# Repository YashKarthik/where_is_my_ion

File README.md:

# Where is my ION???

## LED <-> Driver assignment

1. Driver 1 - 16
    + [x] 1: Conestoga Mall
    + [x] 2: conn to northfield
    + [x] 1: Northfield
    + [x] 3: northfield to r&t
    + [x] 1: R & T
    + [x] 2: r&t to uw
    + [x] 1: UW
    + [x] 1: uw to laurier-waterloo park
    + [x] 1: Laurier-Waterloo Park Stn.
    + [x] 1: laurier-waterloo park to willis way
    + [x] 1: Willis Way Stn.
    + [x] 1: Allen Stn.

2. Driver 2 - 16
    + [x] 1: allen to grh
    + [x] 1: GRH Stn.
    + [x] 2: grh to central
    + [x] 1: Central Stn.
    + [x] 1: Victoria Stn.
    + [x] 1: Queen Stn.
    + [x] 1: Kitchener-Market Stn.
    + [x] 2: kitchener-market to borden
    + [x] 1: Borden Stn.
    + [x] 2: borden to mill
    + [x] 1: Mill Stn.
    + 
    +

3. Driver 3 - 16
    + [x] 3: mill to block line
    + [x] 1: Block Line Stn.
    + [x] 3: block line to fairway
    + [x] 1: Fairway Stn.
-----------reverse
    + [x] 1: Fairway Stn.
    + [x] 3: fairway to block line
    + [x] 1: Block Line Stn.
    + [x] 3: block line to mill

4. Driver 4 - 16
    + [x] 1: Mill Stn.
    + [x] 1: mill to borden
    + [x] 1: Borden Stn.
    + [x] 2: borden to kitchener-market
    + [x] 1: Kitchener-Market Stn.
    + [x] 0: kitchener-market to frederick
    + [x] 1: Frederick Stn.
    + [x] 0: frederick to kitchener city hall
    + [x] 1: Kitchener City Hall Stn.
    + [x] 0: kitchener city hall to central station
    + [x] 1: Central Stn.
    + [x] 2: central to grand river hospital
    + [x] 1: Grand River Hospital Stn.
    + [x] 1: grand river hospital to allen
    + [x] 1: Allen Stn.
    + [x] 0: allen to waterloo public square
    + [x] 1: Waterloo Public Square Stn.
    + [x] 1: waterloo public square to laurier-waterloo park

5. Driver 5 - 14
    + [x] 1: Laurier-Waterloo Park Stn.
    + [x] 1: laurier-waterloo park to university of waterloo
    + [x] 1: University of Waterloo Stn.
    + [x] 2: university of waterloo to research & tech
    + [x] 1: Research & Tech Stn.
    + [x] 3: research & tech to northfield
    + [x] 1: Northfield Stn.
    + [x] 2: northfield to conestoga
    + [x] 1: Conestoga Stn.
    + [x] 1: WIFI (on/off green)

## Num. LED Calculations

- [x] 16 station leds (c -> f) (blue)
- [x] 16 station leds (f -> c) (blue)
- [x] 21 inter-station leds (c -> f) (white)
- [x] 21 inter-station leds (f -> c) (white)
- [x] 1 red/green => 2 leds (power (ON/OFF))
- [x] 1 green wifi (ON/OFF)

= 78/80 used

### Inter-station LEDs

Conestoga to Fairway
- Conestoga to Northfield: 2 leds
- Northfield to Research & Tech: 3 leds
- Research & Tech to University of Waterloo: 2 leds
- University of Waterloo to Laurier-Waterloo Park: 1 led
- Laurier-Waterloo Park to Willis Way: 1 led
- Willis Way to Allen: 0 led
- Allen to Grand River Hospital: 1 led
- Grand River Hospital to Central Station: 2 leds
- Central Station to Victoria Park (0 led)
- Victoria Park to Queen (0 led)
- Queen to Kitchener-Market (0 led)
- Kitchener Market to Borden (2 led)
- Borden to Mill (1 led)
- Mill to Block Line (3 leds)
- Block Line to Fairway (3 ledss)

Fairway to Conestoga
- Fairway to block line (3 leds)
- Block Line to Mill (3 leds)
- Mill to Borden (1 led)
- Borden to Kitchener-Market (2 led)
- Kitchener-Market to Frederick (0 led)
- Frederick to Kitchener City Hall (0 led)
- Kitchener City Hall to Central Station (0 led)
- Central Station to Grand River Hospital:  2 leds
- Grand River Hospital to Allen: 1 led
- Allen to Waterloo Public Sq: 0 led
- Waterloo Public Sq to Laurier-Waterloo Park: 1 led
- Laurier-Waterloo Park to University of Waterloo to : 1 led
- University of Waterloo to Research & Tech:  2 leds
- Research & Tech to Northfield: 3 leds
- Northfield to Conestoga:  2 leds

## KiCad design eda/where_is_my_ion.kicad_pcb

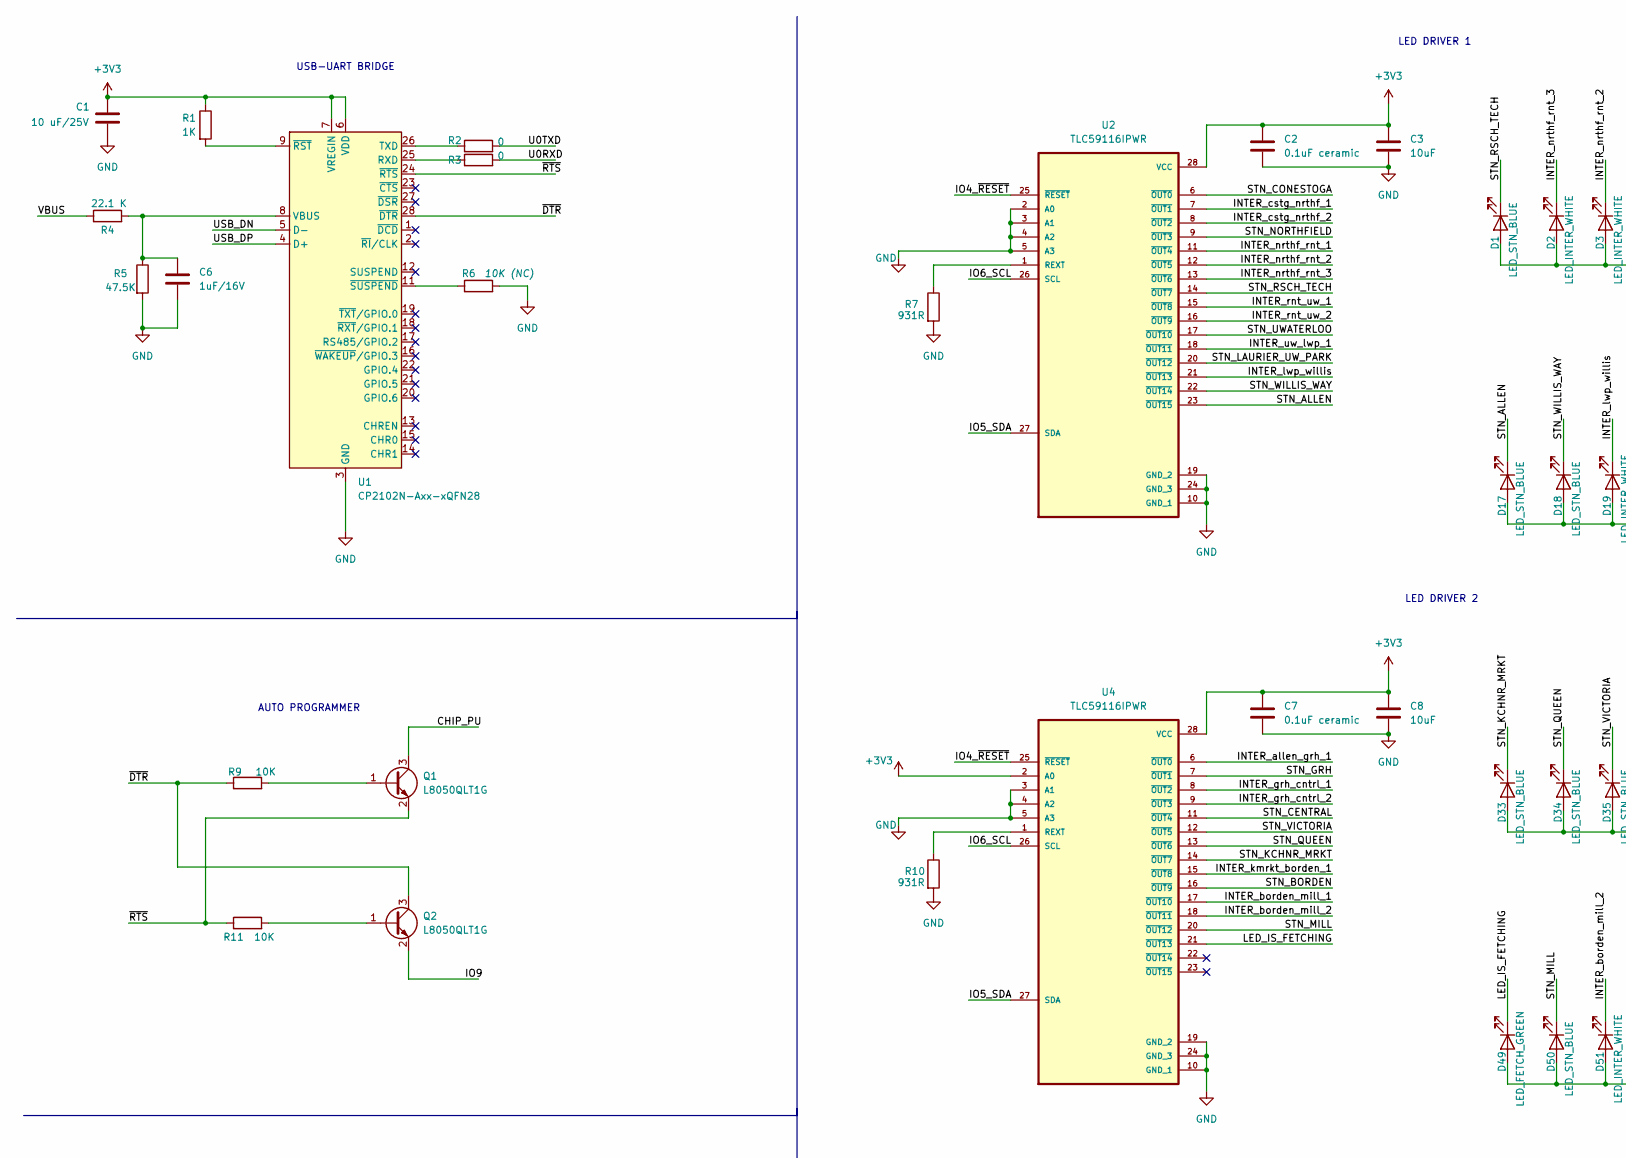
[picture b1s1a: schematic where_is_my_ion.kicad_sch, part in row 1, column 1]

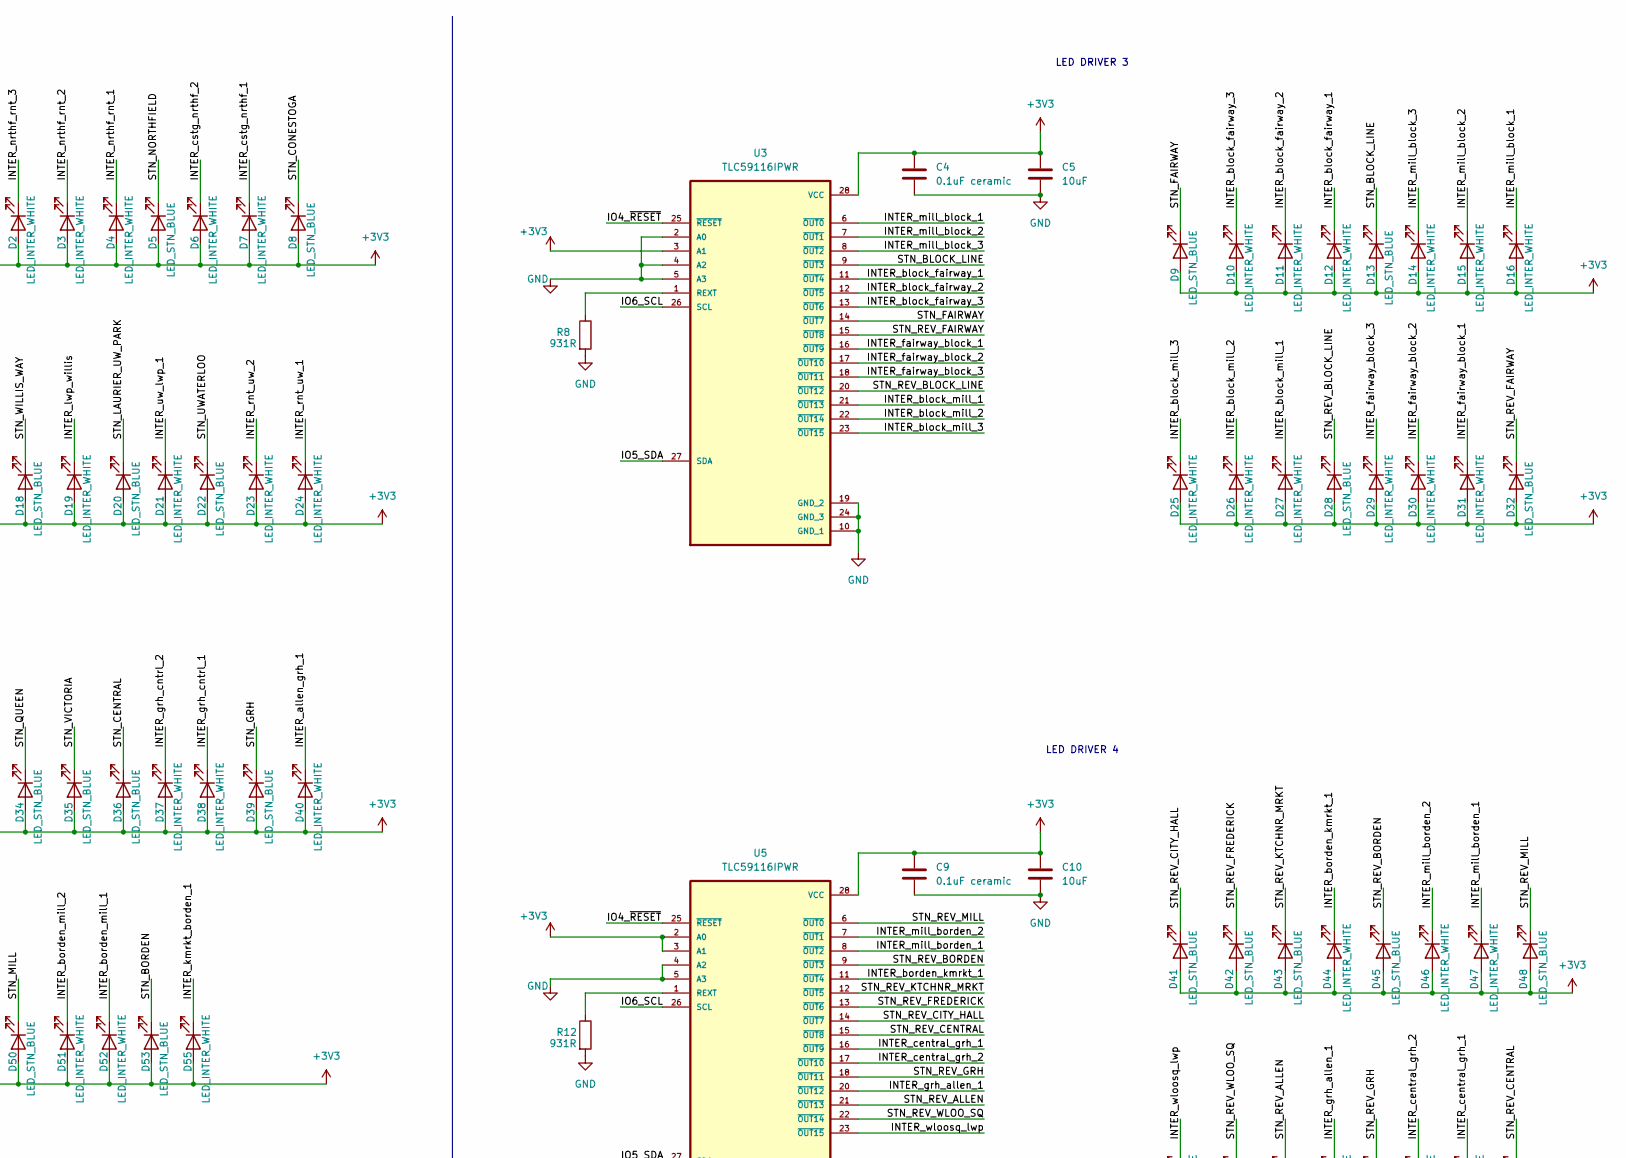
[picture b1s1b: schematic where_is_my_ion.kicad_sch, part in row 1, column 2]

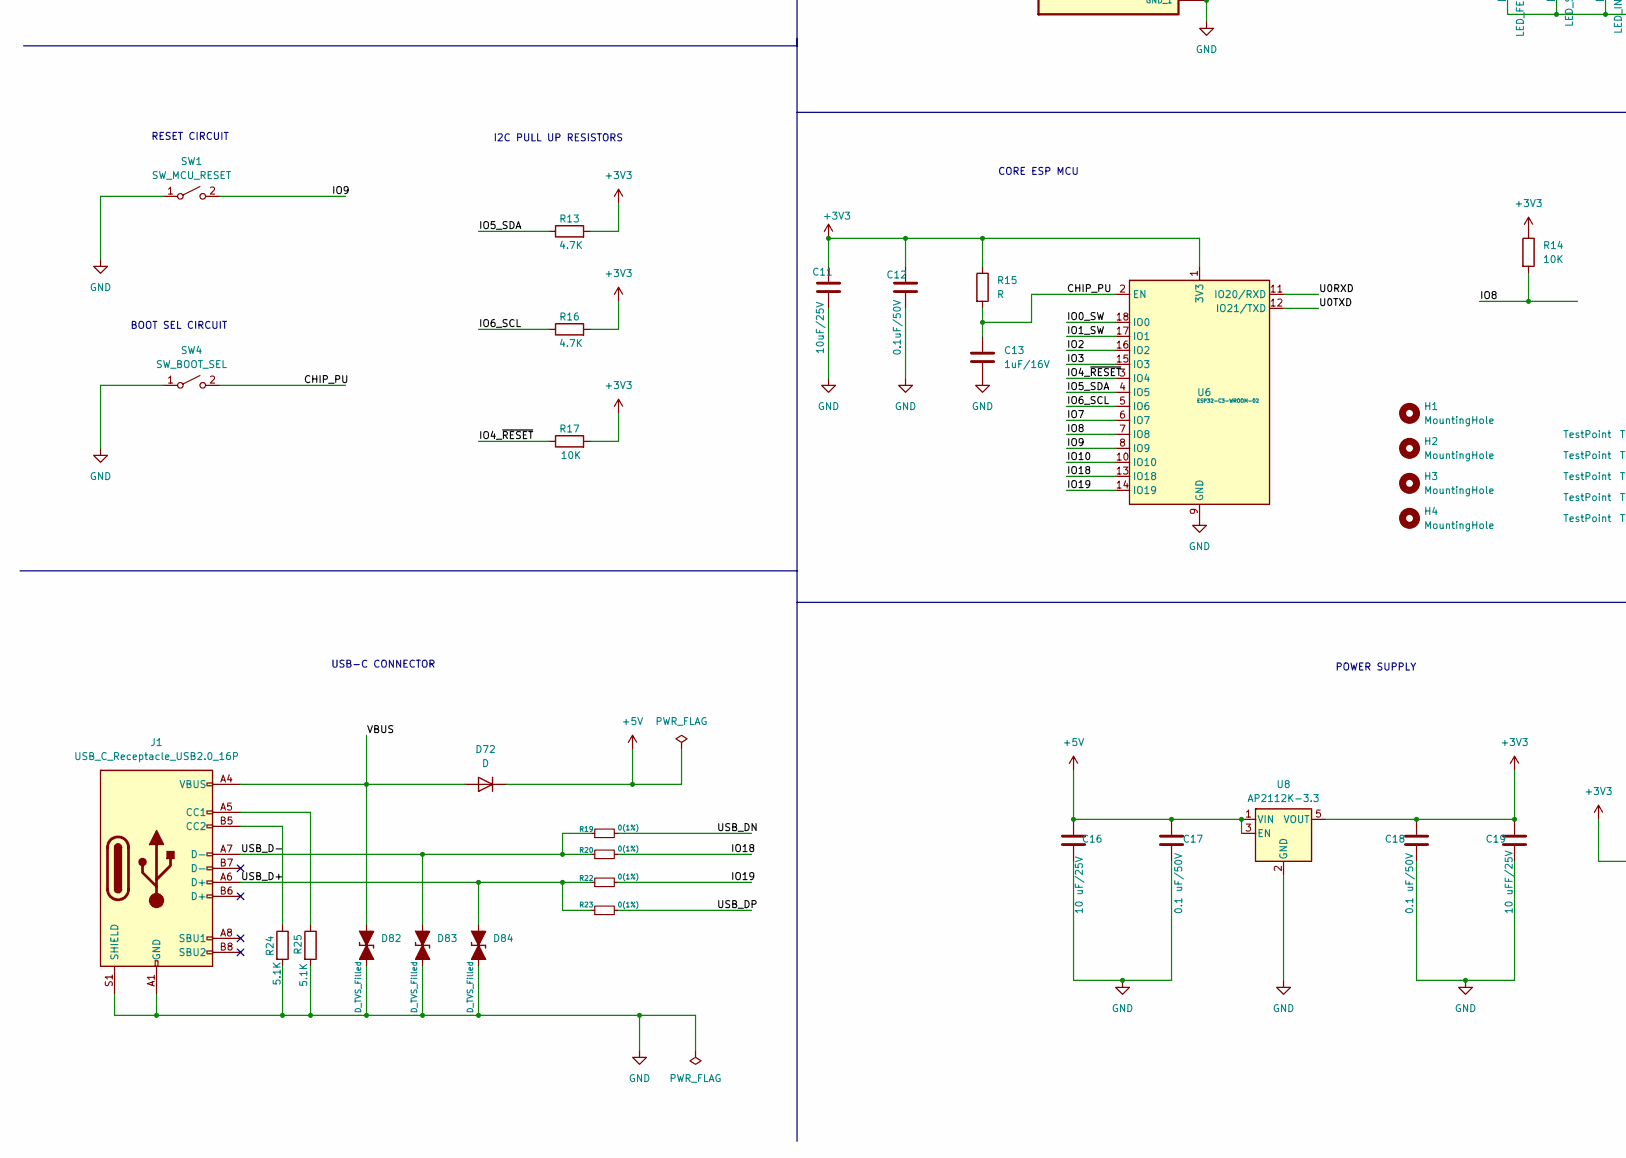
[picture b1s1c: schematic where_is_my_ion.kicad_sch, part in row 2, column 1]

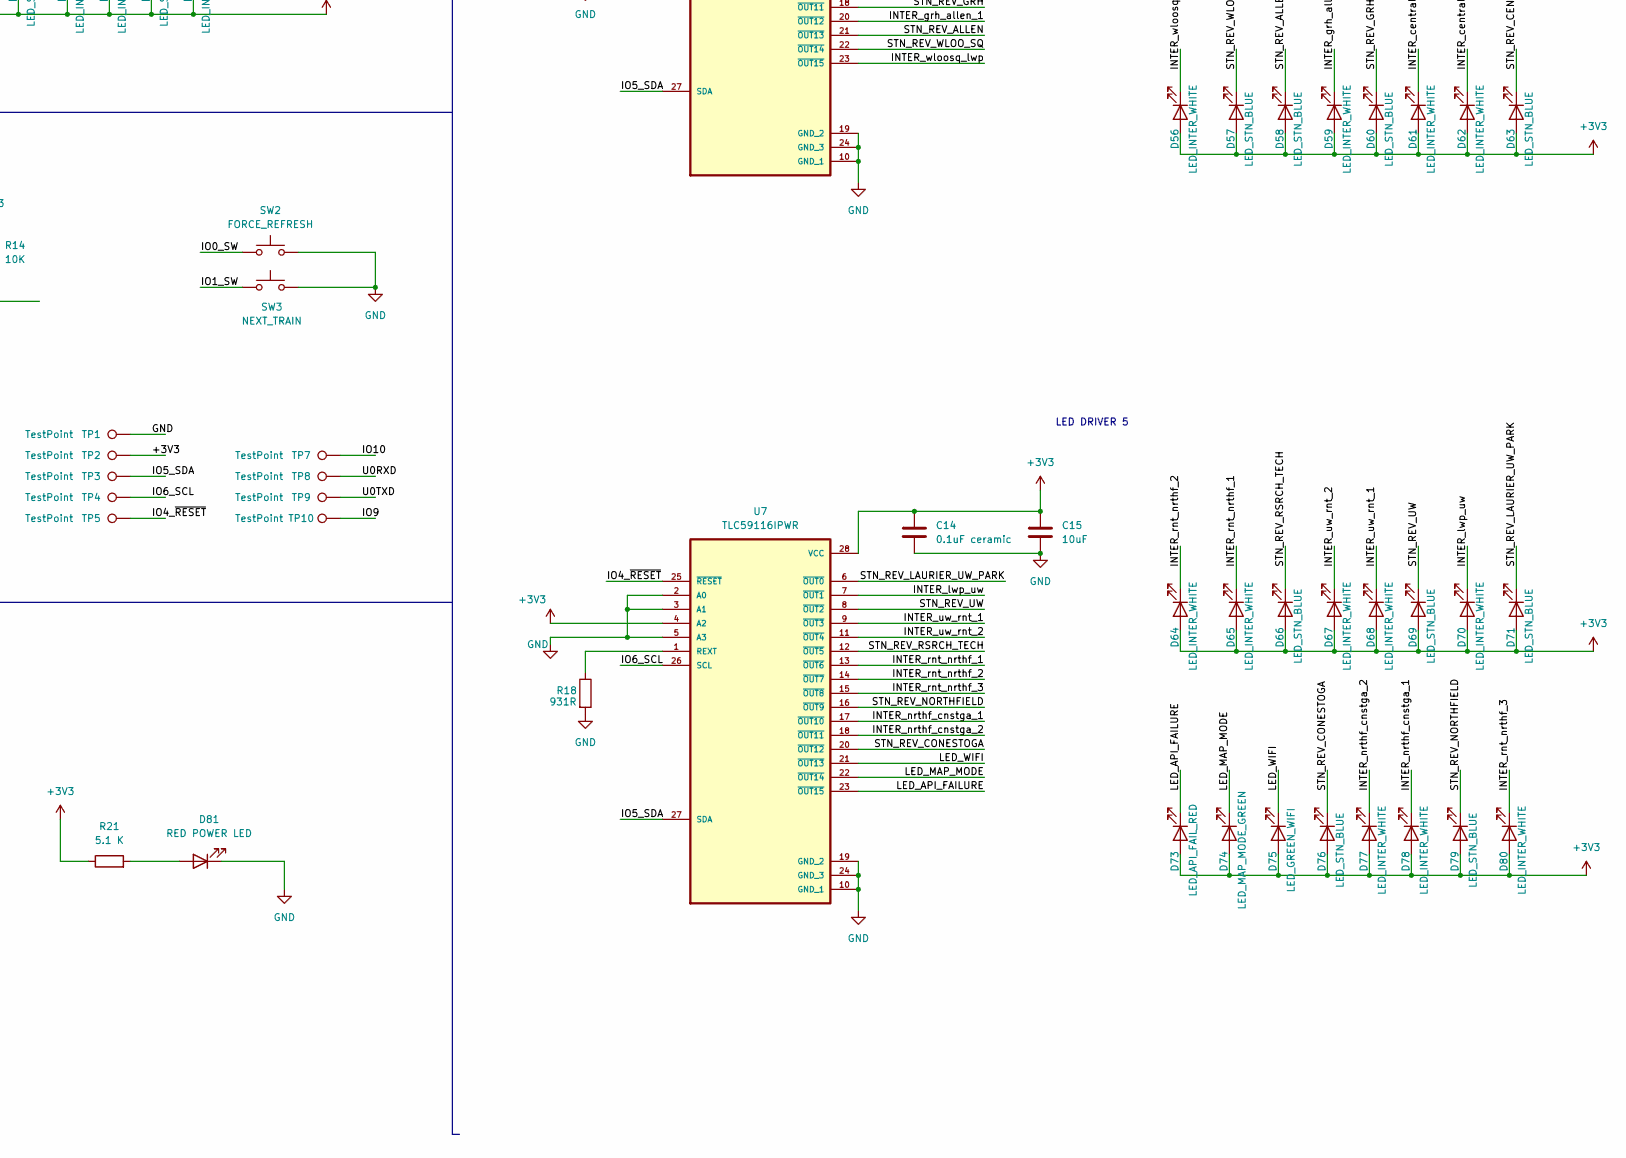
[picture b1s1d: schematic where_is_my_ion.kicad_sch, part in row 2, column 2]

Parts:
C1: 10 uF/25V; CP_EIA-3528-15_AVX-H; LCSC Part Num. C22387953
C2, C4, C7, C9, C14: 0.1uF ceramic; C_0603_1608Metric
C3, C5, C8, C10, C15: 10uF; CP_EIA-3528-15_AVX-H
C6, C13: 1uF/16V; C_0805_2012Metric; LCSC Part Num. C24123
C11: 10uF/25V; CP_EIA-3528-15_AVX-H; LCSC Part Num. C22387953
C12: 0.1uF/50V; C_0603_1608Metric; LCSC Part Num. C3011652
C16: 10 uF/25V; CP_EIA-3528-15_AVX-H
C17, C18: 0.1 uF/50V; C_0603_1608Metric
C19: 10 uFF/25V; CP_EIA-3528-15_AVX-H
D1: LED_STN_BLUE; LED_0603_1608Metric; LCSC Part Num. C497940
D2: LED_INTER_WHITE; LED_0603_1608Metric; LCSC Part Num. C965808
D3, D4, D6, D7, D10, D11, D12, D14, D15, D16, D19, D21, D23, D24, D25, D26, D27, D29, D30, D31, D37, D38, D40, D44, D46, D47, D51, D52, D55, D56, D59, D61, D62, D64, D65, D67, D68, D70, D77, D78, D80: LED_INTER_WHITE; LED_0603_1608Metric
D5, D8, D9, D13, D17, D18, D20, D22, D28, D32, D33, D34, D35, D36, D39, D41, D42, D43, D45, D48, D50, D53, D57, D58, D60, D63, D66, D69, D71, D76, D79: LED_STN_BLUE; LED_0603_1608Metric
D49: LED_FETCH_GREEN; LED_0603_1608Metric; LCSC Part Num. C7429914
D72: D; D_SOD-123; LCSC Part Num. C82544
D73: LED_API_FAIL_RED; LED_0603_1608Metric
D74: LED_MAP_MODE_GREEN; LED_0603_1608Metric
D75: LED_GREEN_WIFI; LED_0603_1608Metric
D81: RED POWER LED; LED_0603_1608Metric; LCSC Part Num. C965799
D82: D_TVS_Filled; D_SOD-523; LCSC Part Num. C383211
D83, D84: D_TVS_Filled; D_SOD-523
H1, H2, H3, H4: MountingHole; MountingHole_2.2mm_M2
J1: USB_C_Receptacle_USB2.0_16P; USB_C_Receptacle_HRO_TYPE-C-31-M-12
Q1, Q2: L8050QLT1G; SOT-23
R1: 1K; R_0603_1608Metric; LCSC Part Num. C22548
R2, R3: 0; R_0603_1608Metric
R4: 22.1 K; R_0603_1608Metric; LCSC Part Num. C137768
R5: 47.5K; R_0603_1608Metric; LCSC Part Num. C2933225
R6: 10K (NC); R_0603_1608Metric
R7, R8, R10, R12, R18: 931R; R_0603_1608Metric
R9, R11, R14, R17: 10K; R_0603_1608Metric
R13, R16: 4.7K; R_0603_1608Metric
R15: R; R_0603_1608Metric
R19, R20, R22, R23: 0(1%); R_0603_1608Metric
R21: 5.1 K; R_0603_1608Metric
R24, R25: 5.1K; R_0603_1608Metric
SW1: SW_MCU_RESET; SW_TS-1088-AR02016_1
SW2: FORCE_REFRESH; SW_TS-1088-AR02016_1
SW3: NEXT_TRAIN; SW_TS-1088-AR02016_1
SW4: SW_BOOT_SEL; SW_TS-1088-AR02016_1
TP1, TP2, TP3, TP4, TP5, TP7, TP8, TP9, TP10: TestPoint; TestPoint_Pad_D2.0mm
U1: CP2102N-Axx-xQFN28; QFN-28-1EP_5x5mm_P0.5mm_EP3.35x3.35mm
U2, U3, U4, U5, U7: TLC59116IPWR; SOP65P640X120-28N
U6: ESP32-C3-WROOM-02
U8: AP2112K-3.3; SOT-23-5

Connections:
+3V3: C1.1, C2.1, C3.1, C4.1, C5.1, C7.1, C8.1, C9.1, C10.1, C11.1, C12.1, C14.1, C15.1, C18.2, C19.1, D1.2 (A), D2.2 (A), D3.2 (A), D4.2 (A), D5.2 (A), D6.2 (A), D7.2 (A), D8.2 (A), D9.2 (A), D10.2 (A), D11.2 (A), D12.2 (A), D13.2 (A), D14.2 (A), D15.2 (A), D16.2 (A), D17.2 (A), D18.2 (A), D19.2 (A), D20.2 (A), D21.2 (A), D22.2 (A), D23.2 (A), D24.2 (A), D25.2 (A), D26.2 (A), D27.2 (A), D28.2 (A), D29.2 (A), D30.2 (A), D31.2 (A), D32.2 (A), D33.2 (A), D34.2 (A), D35.2 (A), D36.2 (A), D37.2 (A), D38.2 (A), D39.2 (A), D40.2 (A), D41.2 (A), D42.2 (A), D43.2 (A), D44.2 (A), D45.2 (A), D46.2 (A), D47.2 (A), D48.2 (A), D49.2 (A), D50.2 (A), D51.2 (A), D52.2 (A), D53.2 (A), D55.2 (A), D56.2 (A), D57.2 (A), D58.2 (A), D59.2 (A), D60.2 (A), D61.2 (A), D62.2 (A), D63.2 (A), D64.2 (A), D65.2 (A), D66.2 (A), D67.2 (A), D68.2 (A), D69.2 (A), D70.2 (A), D71.2 (A), D73.2 (A), D74.2 (A), D75.2 (A), D76.2 (A), D77.2 (A), D78.2 (A), D79.2 (A), D80.2 (A), R1.1, R13.2, R14.1, R15.1, R16.2, R17.2, R21.1, TP2.1, U1.6 (VDD), U1.7 (VREGIN), U2.28 (VCC), U3.3 (A1), U3.28 (VCC), U4.2 (A0), U4.28 (VCC), U5.2 (A0), U5.3 (A1), U5.28 (VCC), U6.1 (3V3), U7.4 (A2), U7.28 (VCC), U8.5 (VOUT)
+5V: C16.1, C17.2, D72.1 (K), U8.1 (VIN), U8.3 (EN)
/CHIP_PU: C13.1, Q1.3 (C), R15.2, SW4.2 (B), U6.2 (EN)
/INTER_allen_grh_1: D40.1 (K), U4.6 (~OUT0)
/INTER_block_fairway_1: D12.1 (K), U3.11 (~OUT4)
/INTER_block_fairway_2: D11.1 (K), U3.12 (~OUT5)
/INTER_block_fairway_3: D10.1 (K), U3.13 (~OUT6)
/INTER_block_mill_1: D27.1 (K), U3.21 (~OUT13)
/INTER_block_mill_2: D26.1 (K), U3.22 (~OUT14)
/INTER_block_mill_3: D25.1 (K), U3.23 (~OUT15)
/INTER_borden_kmrkt_1: D44.1 (K), U5.11 (~OUT4)
/INTER_borden_mill_1: D52.1 (K), U4.17 (~OUT10)
/INTER_borden_mill_2: D51.1 (K), U4.18 (~OUT11)
/INTER_central_grh_1: D62.1 (K), U5.16 (~OUT9)
/INTER_central_grh_2: D61.1 (K), U5.17 (~OUT10)
/INTER_cstg_nrthf_1: D7.1 (K), U2.7 (~OUT1)
/INTER_cstg_nrthf_2: D6.1 (K), U2.8 (~OUT2)
/INTER_fairway_block_1: D31.1 (K), U3.16 (~OUT9)
/INTER_fairway_block_2: D30.1 (K), U3.17 (~OUT10)
/INTER_fairway_block_3: D29.1 (K), U3.18 (~OUT11)
/INTER_grh_allen_1: D59.1 (K), U5.20 (~OUT12)
/INTER_grh_cntrl_1: D38.1 (K), U4.8 (~OUT2)
/INTER_grh_cntrl_2: D37.1 (K), U4.9 (~OUT3)
/INTER_kmrkt_borden_1: D55.1 (K), U4.15 (~OUT8)
/INTER_lwp_uw: D70.1 (K), U7.7 (~OUT1)
/INTER_lwp_willis: D19.1 (K), U2.21 (~OUT13)
/INTER_mill_block_1: D16.1 (K), U3.6 (~OUT0)
/INTER_mill_block_2: D15.1 (K), U3.7 (~OUT1)
/INTER_mill_block_3: D14.1 (K), U3.8 (~OUT2)
/INTER_mill_borden_1: D47.1 (K), U5.8 (~OUT2)
/INTER_mill_borden_2: D46.1 (K), U5.7 (~OUT1)
/INTER_nrthf_cnstga_1: D78.1 (K), U7.17 (~OUT10)
/INTER_nrthf_cnstga_2: D77.1 (K), U7.18 (~OUT11)
/INTER_nrthf_rnt_1: D4.1 (K), U2.11 (~OUT4)
/INTER_nrthf_rnt_2: D3.1 (K), U2.12 (~OUT5)
/INTER_nrthf_rnt_3: D2.1 (K), U2.13 (~OUT6)
/INTER_rnt_nrthf_1: D65.1 (K), U7.13 (~OUT6)
/INTER_rnt_nrthf_2: D64.1 (K), U7.14 (~OUT7)
/INTER_rnt_nrthf_3: D80.1 (K), U7.15 (~OUT8)
/INTER_rnt_uw_1: D24.1 (K), U2.15 (~OUT8)
/INTER_rnt_uw_2: D23.1 (K), U2.16 (~OUT9)
/INTER_uw_lwp_1: D21.1 (K), U2.18 (~OUT11)
/INTER_uw_rnt_1: D68.1 (K), U7.9 (~OUT3)
/INTER_uw_rnt_2: D67.1 (K), U7.11 (~OUT4)
/INTER_wloosq_lwp: D56.1 (K), U5.23 (~OUT15)
/IO0_SW: SW2.1, U6.18 (IO0)
/IO1_SW: SW3.1, U6.17 (IO1)
/IO2: U6.16 (IO2)
/IO3: U6.15 (IO3)
/IO4_~RESET: R17.1, TP5.1, U2.25 (~RESET), U3.25 (~RESET), U4.25 (~RESET), U5.25 (~RESET), U6.3 (IO4), U7.25 (~RESET)
/IO5_SDA: R13.1, TP3.1, U2.27 (SDA), U3.27 (SDA), U4.27 (SDA), U5.27 (SDA), U6.4 (IO5), U7.27 (SDA)
/IO6_SCL: R16.1, TP4.1, U2.26 (SCL), U3.26 (SCL), U4.26 (SCL), U5.26 (SCL), U6.5 (IO6), U7.26 (SCL)
/IO7: U6.6 (IO7)
/IO8: R14.2, U6.7 (IO8)
/IO9: Q2.2 (E), SW1.2 (B), TP10.1, U6.8 (IO9)
/IO10: TP7.1, U6.10 (IO10)
/IO18: R20.2, U6.13 (IO18)
/IO19: R22.2, U6.14 (IO19)
/LED_API_FAILURE: D73.1 (K), U7.23 (~OUT15)
/LED_IS_FETCHING: D49.1 (K), U4.21 (~OUT13)
/LED_MAP_MODE: D74.1 (K), U7.22 (~OUT14)
/LED_WIFI: D75.1 (K), U7.21 (~OUT13)
/STN_ALLEN: D17.1 (K), U2.23 (~OUT15)
/STN_BLOCK_LINE: D13.1 (K), U3.9 (~OUT3)
/STN_BORDEN: D53.1 (K), U4.16 (~OUT9)
/STN_CENTRAL: D36.1 (K), U4.11 (~OUT4)
/STN_CONESTOGA: D8.1 (K), U2.6 (~OUT0)
/STN_FAIRWAY: D9.1 (K), U3.14 (~OUT7)
/STN_GRH: D39.1 (K), U4.7 (~OUT1)
/STN_KCHNR_MRKT: D33.1 (K), U4.14 (~OUT7)
/STN_LAURIER_UW_PARK: D20.1 (K), U2.20 (~OUT12)
/STN_MILL: D50.1 (K), U4.20 (~OUT12)
/STN_NORTHFIELD: D5.1 (K), U2.9 (~OUT3)
/STN_QUEEN: D34.1 (K), U4.13 (~OUT6)
/STN_REV_ALLEN: D58.1 (K), U5.21 (~OUT13)
/STN_REV_BLOCK_LINE: D28.1 (K), U3.20 (~OUT12)
/STN_REV_BORDEN: D45.1 (K), U5.9 (~OUT3)
/STN_REV_CENTRAL: D63.1 (K), U5.15 (~OUT8)
/STN_REV_CITY_HALL: D41.1 (K), U5.14 (~OUT7)
/STN_REV_CONESTOGA: D76.1 (K), U7.20 (~OUT12)
/STN_REV_FAIRWAY: D32.1 (K), U3.15 (~OUT8)
/STN_REV_FREDERICK: D42.1 (K), U5.13 (~OUT6)
/STN_REV_GRH: D60.1 (K), U5.18 (~OUT11)
/STN_REV_KTCHNR_MRKT: D43.1 (K), U5.12 (~OUT5)
/STN_REV_LAURIER_UW_PARK: D71.1 (K), U7.6 (~OUT0)
/STN_REV_MILL: D48.1 (K), U5.6 (~OUT0)
/STN_REV_NORTHFIELD: D79.1 (K), U7.16 (~OUT9)
/STN_REV_RSRCH_TECH: D66.1 (K), U7.12 (~OUT5)
/STN_REV_UW: D69.1 (K), U7.8 (~OUT2)
/STN_REV_WLOO_SQ: D57.1 (K), U5.22 (~OUT14)
/STN_RSCH_TECH: D1.1 (K), U2.14 (~OUT7)
/STN_UWATERLOO: D22.1 (K), U2.17 (~OUT10)
/STN_VICTORIA: D35.1 (K), U4.12 (~OUT5)
/STN_WILLIS_WAY: D18.1 (K), U2.22 (~OUT14)
/U0RXD: R3.2, TP8.1, U6.11 (IO20/RXD)
/U0TXD: R2.2, TP9.1, U6.12 (IO21/TXD)
/USB_D+: D84.2 (A2), J1.A6 (D+), R22.1, R23.1
/USB_D-: D83.2 (A2), J1.A7 (D-), R19.1, R20.1
/USB_DN: R19.2, U1.5 (D-)
/USB_DP: R23.2, U1.4 (D+)
/VBUS: D72.2 (A), D82.2 (A2), J1.A4 (VBUS), J1.A9 (VBUS), J1.B4 (VBUS), J1.B9 (VBUS), R4.1
/~DTR: Q2.3 (C), R9.1, U1.28 (~DTR)
/~RTS: Q1.2 (E), R11.1, U1.24 (~RTS)
GND: C1.2, C2.2, C3.2, C4.2, C5.2, C6.2, C7.2, C8.2, C9.2, C10.2, C11.2, C12.2, C13.2, C14.2, C15.2, C16.2, C17.1, C18.1, C19.2, D81.1 (K), D82.1 (A1), D83.1 (A1), D84.1 (A1), J1.A1 (GND), J1.A12 (GND), J1.B1 (GND), J1.B12 (GND), J1.S1 (SHIELD), R5.2, R6.2, R7.2, R8.2, R10.2, R12.2, R18.2, R24.2, R25.2, SW1.1 (A), SW2.2, SW3.2, SW4.1 (A), TP1.1, U1.3 (GND), U1.29 (GND), U2.2 (A0), U2.3 (A1), U2.4 (A2), U2.5 (A3), U2.10 (GND_1), U2.19 (GND_2), U2.24 (GND_3), U3.2 (A0), U3.4 (A2), U3.5 (A3), U3.10 (GND_1), U3.19 (GND_2), U3.24 (GND_3), U4.3 (A1), U4.4 (A2), U4.5 (A3), U4.10 (GND_1), U4.19 (GND_2), U4.24 (GND_3), U5.4 (A2), U5.5 (A3), U5.10 (GND_1), U5.19 (GND_2), U5.24 (GND_3), U6.9 (GND), U6.19 (GND), U7.2 (A0), U7.3 (A1), U7.5 (A3), U7.10 (GND_1), U7.19 (GND_2), U7.24 (GND_3), U8.2 (GND)
unnamed: D81.2 (A), R21.2
unnamed: J1.A5 (CC1), R25.1
unnamed: J1.B5 (CC2), R24.1
unnamed: Q1.1 (B), R9.2
unnamed: Q2.1 (B), R11.2
unnamed: R3.1, U1.25 (RXD)
unnamed: R2.1, U1.26 (TXD)
unnamed: C6.1, R4.2, R5.1, U1.8 (VBUS)
unnamed: R1.2, U1.9 (~RST)
unnamed: R6.1, U1.11 (~SUSPEND)
unnamed: R7.1, U2.1 (REXT)
unnamed: R8.1, U3.1 (REXT)
unnamed: R10.1, U4.1 (REXT)
unnamed: R12.1, U5.1 (REXT)
unnamed: R18.1, U7.1 (REXT)

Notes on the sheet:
USB-C CONNECTOR
BOOT SEL CIRCUIT
AUTO PROGRAMMER
LED DRIVER 1
LED DRIVER 2
RESET CIRCUIT
POWER SUPPLY
LED DRIVER 5
USB-UART BRIDGE
LED DRIVER 4
LED DRIVER 3
I2C PULL UP RESISTORS
CORE ESP MCU

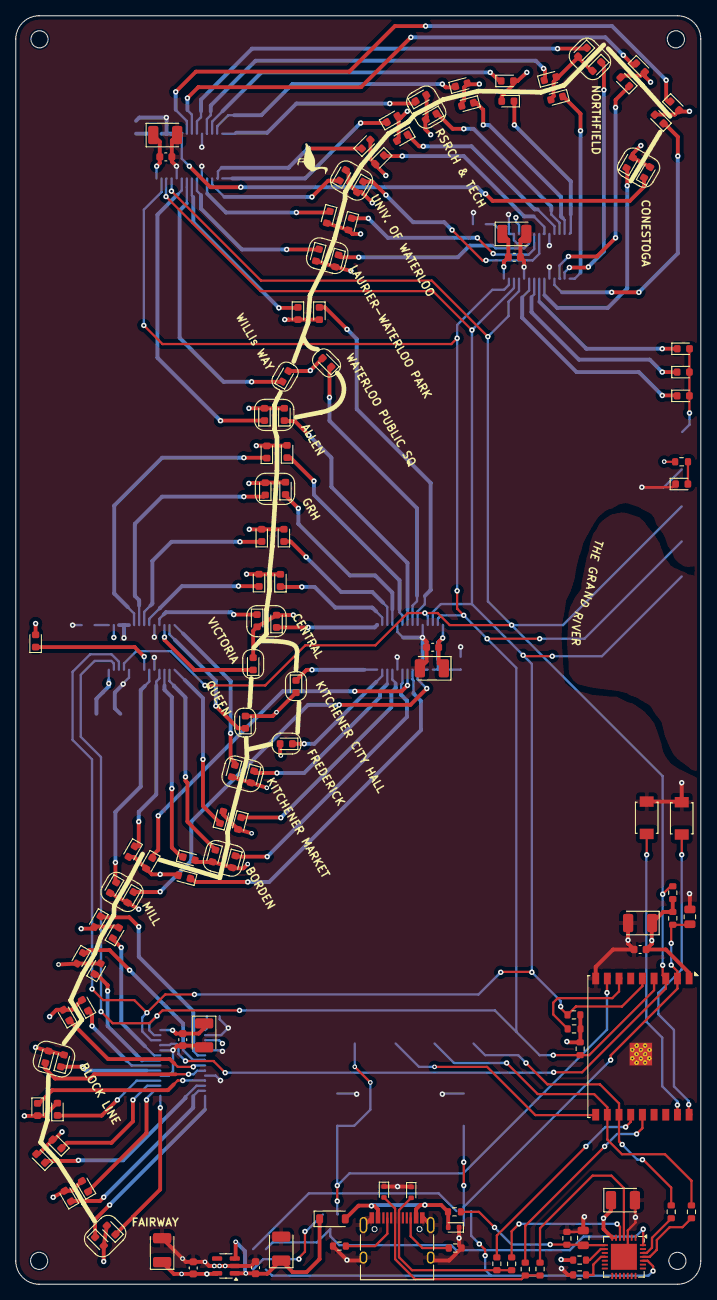
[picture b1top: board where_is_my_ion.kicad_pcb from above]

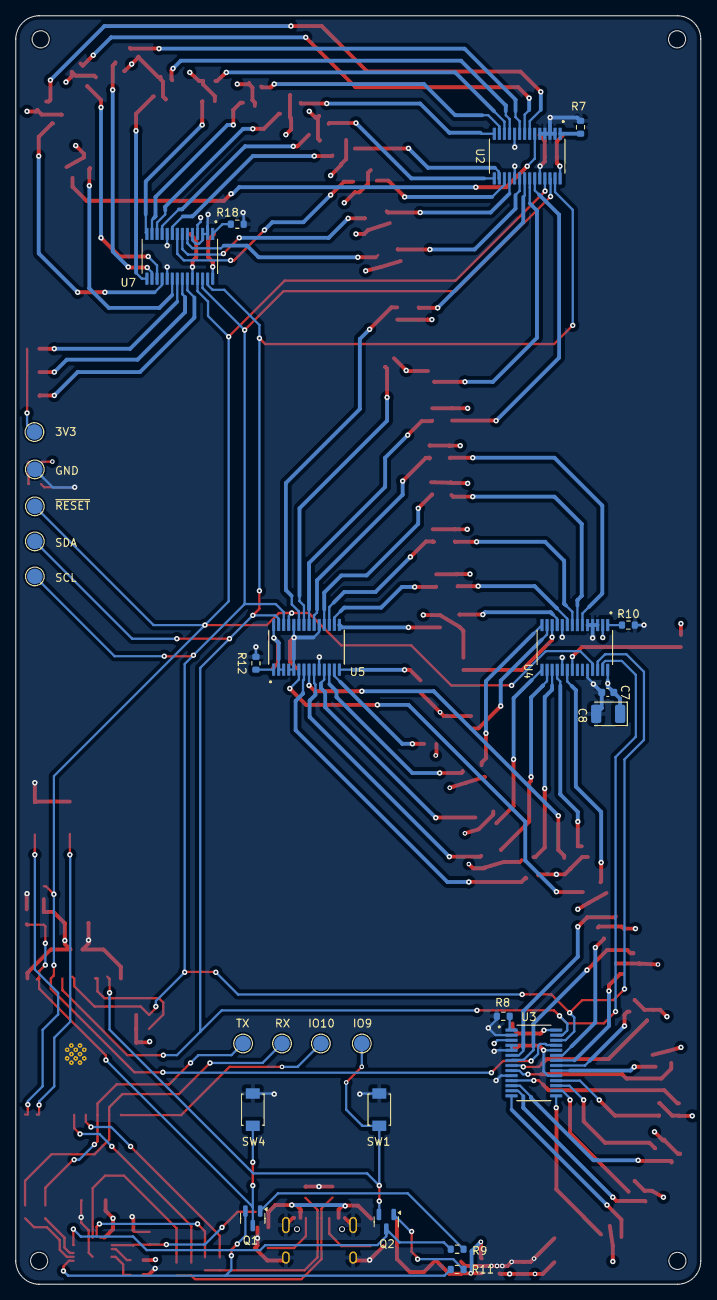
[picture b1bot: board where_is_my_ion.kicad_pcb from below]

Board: 4 copper layers, 88.0 x 163.0 mm, 155 parts (27 on the bottom side), 116 nets.

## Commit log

2025-01-31 13k lines of codegen!!
2025-02-16 got some stuff working; use make; cmake in future maybe
2025-02-16 generate lookup table for (trip_id, seq) -> Stop
2025-02-16 status inducators
2025-03-30 schematic done?
2025-03-30 final sch
2025-04-08 stuff
2025-04-10 routing is hard
2025-04-17 almost done; might have to redo driver2
2025-04-19 might change
2025-04-19 side by side layout
2025-04-20 nearly done
2025-04-21 almost done, just silkscreen now
2025-04-22 comit:wq
2025-04-22 more silk
2025-05-14 probably done
